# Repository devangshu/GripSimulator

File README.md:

# Grip Simulator

EE445L Final Project by Stefanie Thompson, Devangshu Goswami, Pulkit Mahajan, Anuv Gupta

## Notes

-   Password secret: `grip`
-   Serial format: `vpNum=vpValueNew\n` as `__=___...\n` ie. `03=245\n` or `12=1005\n`
    -   Two digits to represent the virtual pin number, then the full virtual pin integer value (any # of digits) followed by a newline character `\n`

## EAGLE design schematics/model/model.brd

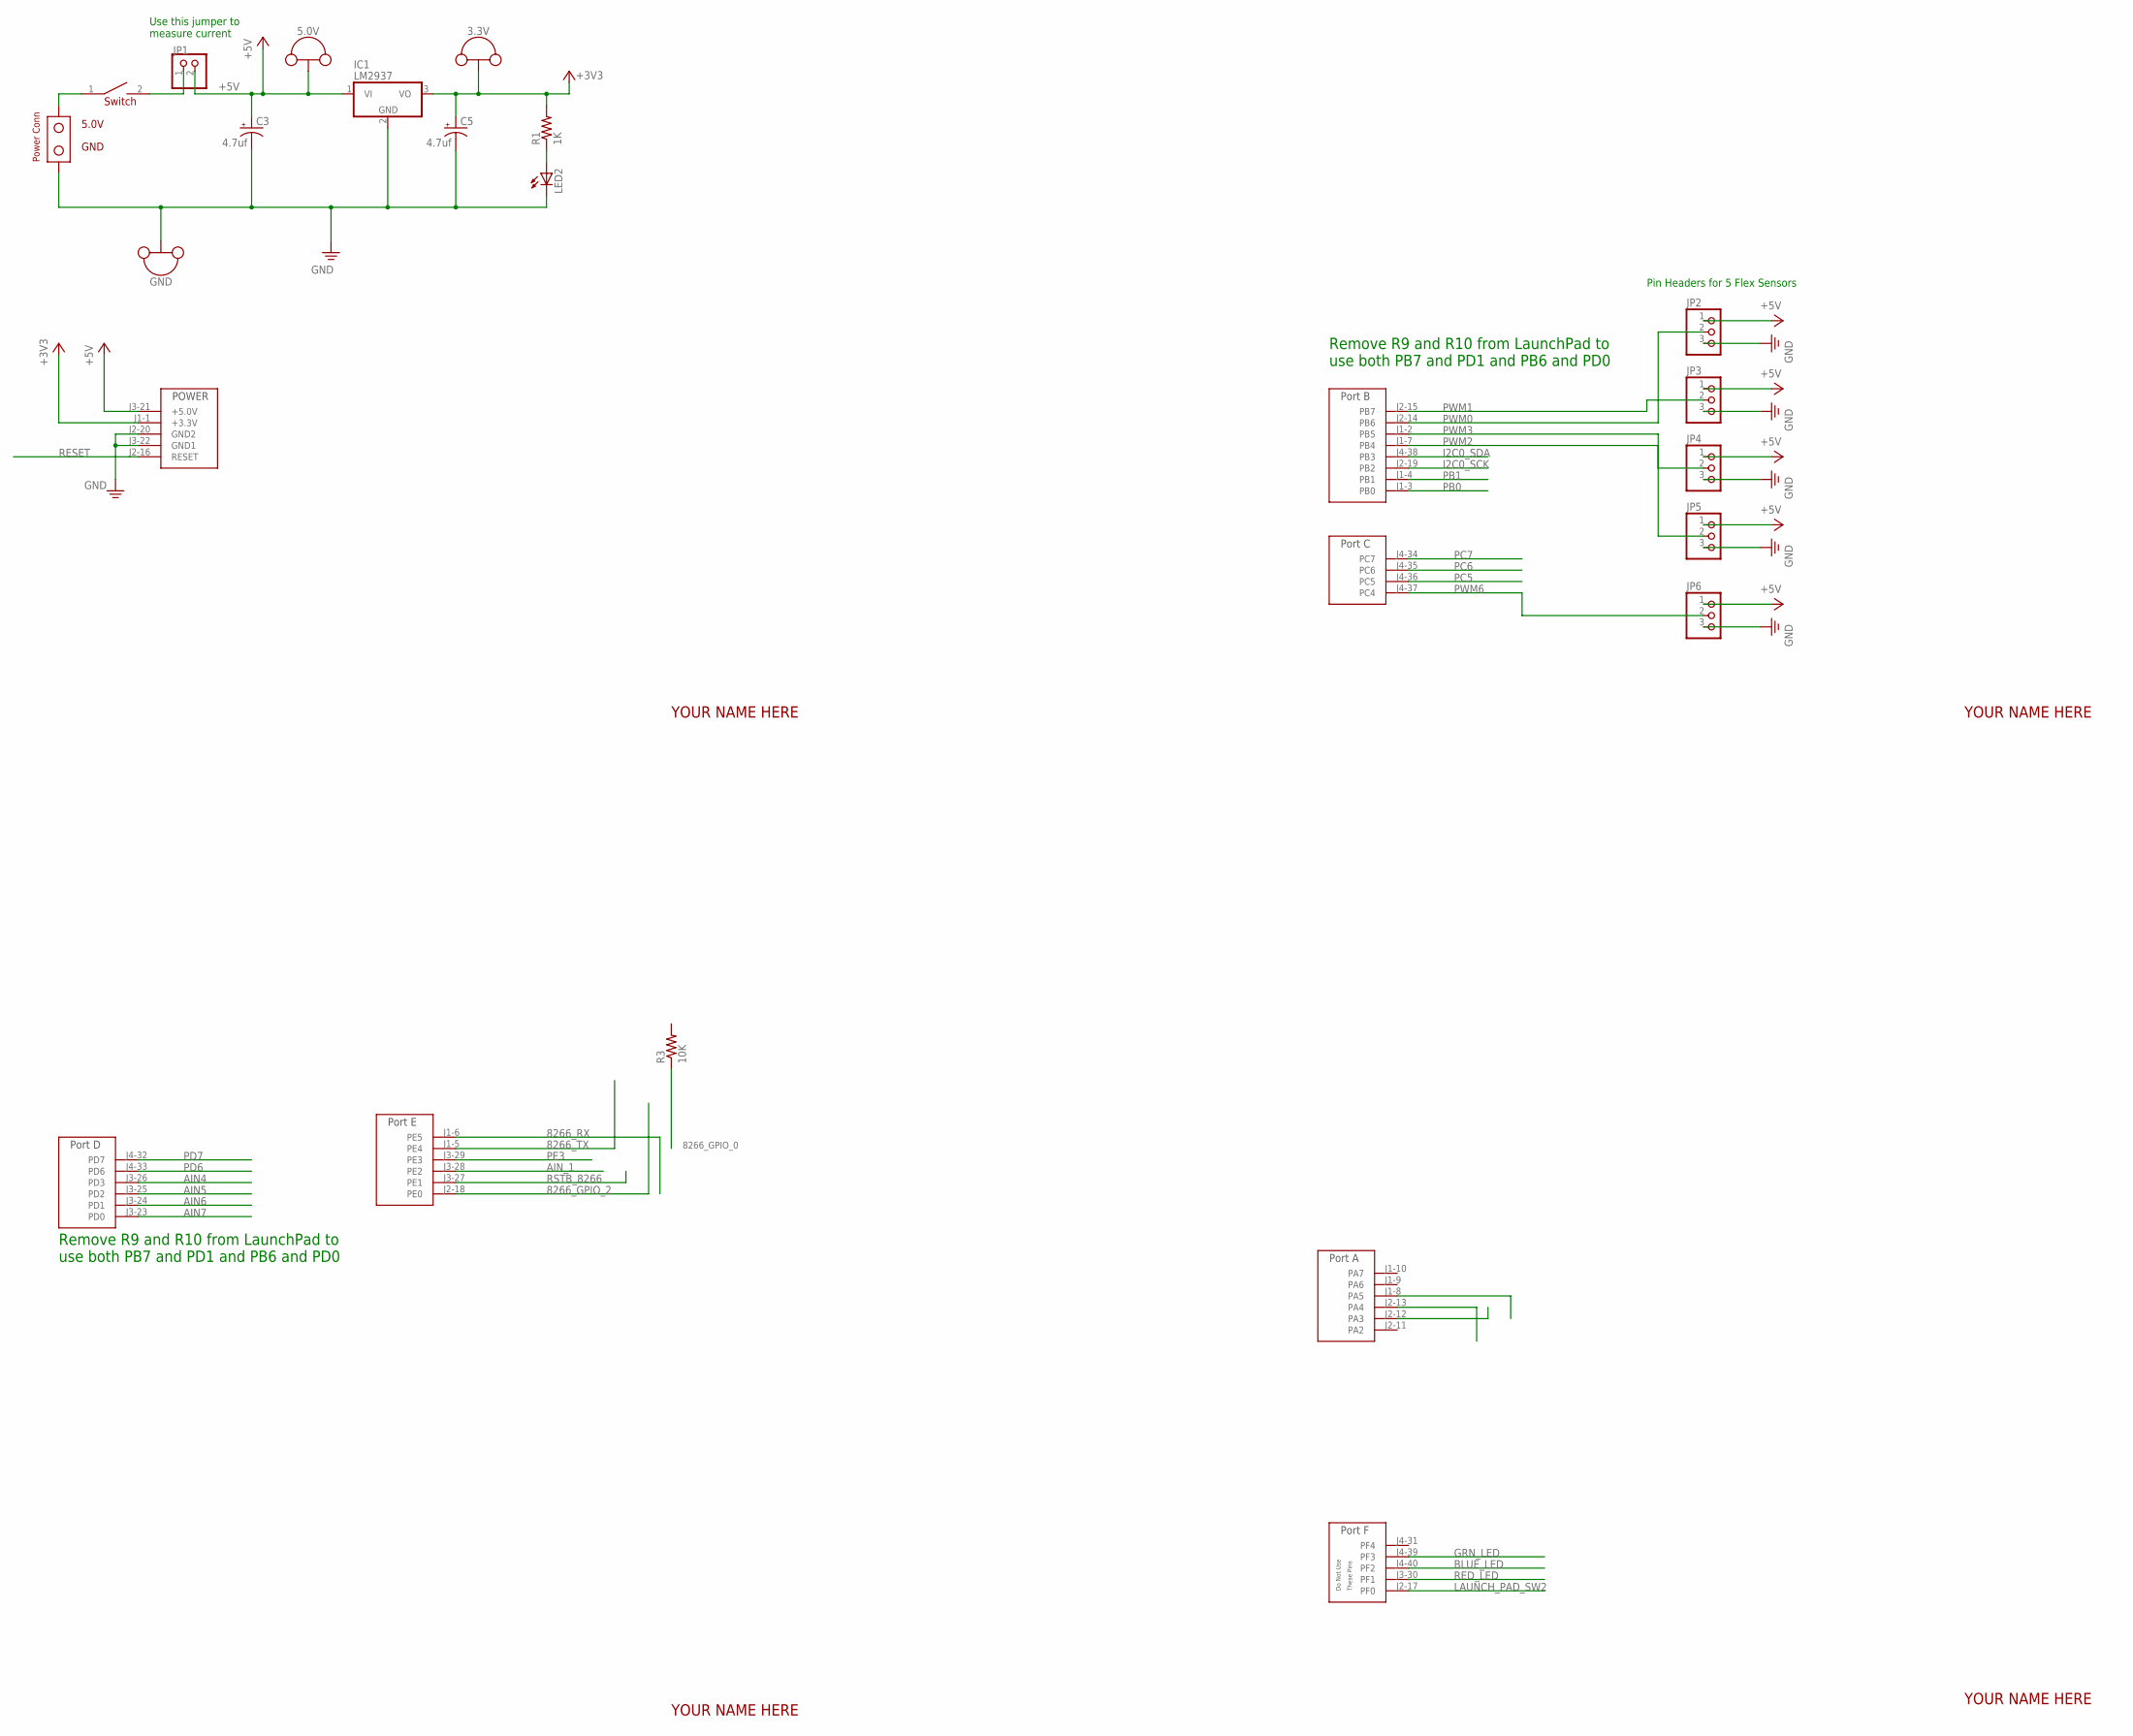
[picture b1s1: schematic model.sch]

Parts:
3.3V, 5.0V: TP_LOOP
C3, C5: 4.7uf; CAP200MILPOLARIZED
GND: TP_LOOP
IC1: LM2937; TO220
JP1: PINHD-1X2; 1X02
JP2, JP3, JP4, JP5, JP6: PINHD-1X3; 1X03
LED2: LED3MM
R1: 1K; RES200MIL
R3: 10K; RES300MIL
U$2: TM4C_BP; TM4C_BOOSTER_PACK
U$5: POWER_CONN
U$6: SW_POWER_100MIL; SW_POWER

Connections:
8266_GPIO_0: R3.1
8266_GPIO_2: U$2.J2-18 (PE0)
8266_RX: U$2.J1-6 (PE5)
8266_TX: U$2.J1-5 (PE4)
+3V3: 3.3V.P$1, 3.3V.P$2, C5.+, IC1.3 (VO), R1.2, U$2.J1-1 (+3.3V)
+5V: 5.0V.P$1, 5.0V.P$2, C3.+, IC1.1 (VI), JP1.2, JP2.1, JP3.1, JP4.1, JP5.1, JP6.1, U$2.J3-21 (+5.0V)
AIN4: U$2.J3-26 (PD3)
AIN5: U$2.J3-25 (PD2)
AIN6: U$2.J3-24 (PD1)
AIN7: U$2.J3-23 (PD0)
AIN_1: U$2.J3-28 (PE2)
BLUE_LED: U$2.J4-40 (PF2)
GND: C3.-, C5.-, GND.P$1, GND.P$2, IC1.2 (GND), JP2.3, JP3.3, JP4.3, JP5.3, JP6.3, LED2.K (C), U$2.J2-20 (GND2), U$2.J3-22 (GND1), U$5.GND
GRN_LED: U$2.J4-39 (PF3)
I2C0_SCK: U$2.J2-19 (PB2)
I2C0_SDA: U$2.J4-38 (PB3)
LAUNCH_PAD_SW2: U$2.J2-17 (PF0)
unnamed: JP1.1, U$6.2
unnamed: LED2.A, R1.1
unnamed: U$5.VDD, U$6.1
PB0: U$2.J1-3 (PB0)
PB1: U$2.J1-4 (PB1)
PC5: U$2.J4-36 (PC5)
PC6: U$2.J4-35 (PC6)
PC7: U$2.J4-34 (PC7)
PD6: U$2.J4-33 (PD6)
PD7: U$2.J4-32 (PD7)
PE3: U$2.J3-29 (PE3)
PWM0: JP2.2, U$2.J2-14 (PB6)
PWM1: JP3.2, U$2.J2-15 (PB7)
PWM2: JP4.2, U$2.J1-7 (PB4)
PWM3: JP5.2, U$2.J1-2 (PB5)
PWM6: JP6.2, U$2.J4-37 (PC4)
RED_LED: U$2.J3-30 (PF1)
RESET: U$2.J2-16 (RESET)
RSTB_8266: U$2.J3-27 (PE1)
ST7735_MISO: U$2.J2-13 (PA4)
ST7735_MOSI: U$2.J1-8 (PA5)
ST7735_TFT_CS: U$2.J2-12 (PA3)

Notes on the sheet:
Use this jumper to measure current
Remove R9 and R10 from LaunchPad to use both PB7 and PD1 and PB6 and PD0
YOUR NAME HERE
Pin Headers for 5 Flex Sensors

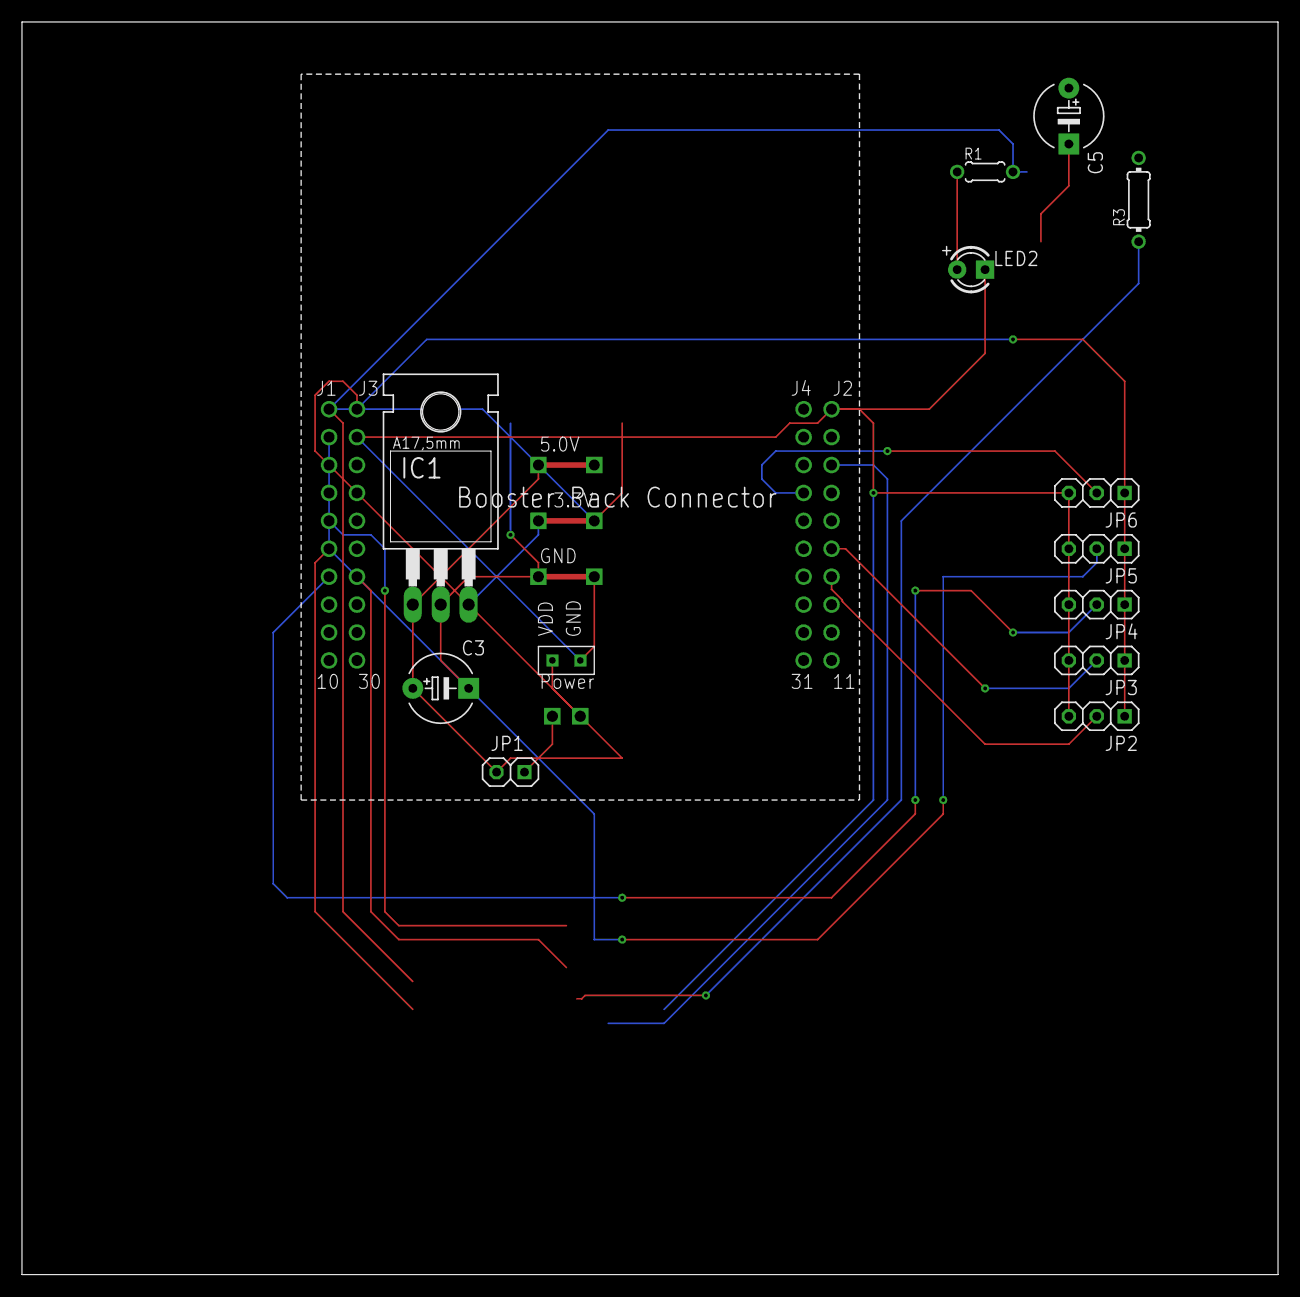
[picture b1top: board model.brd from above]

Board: 2 copper layers, 114.3 x 114.0 mm, 18 parts (0 on the bottom side), 11 nets.

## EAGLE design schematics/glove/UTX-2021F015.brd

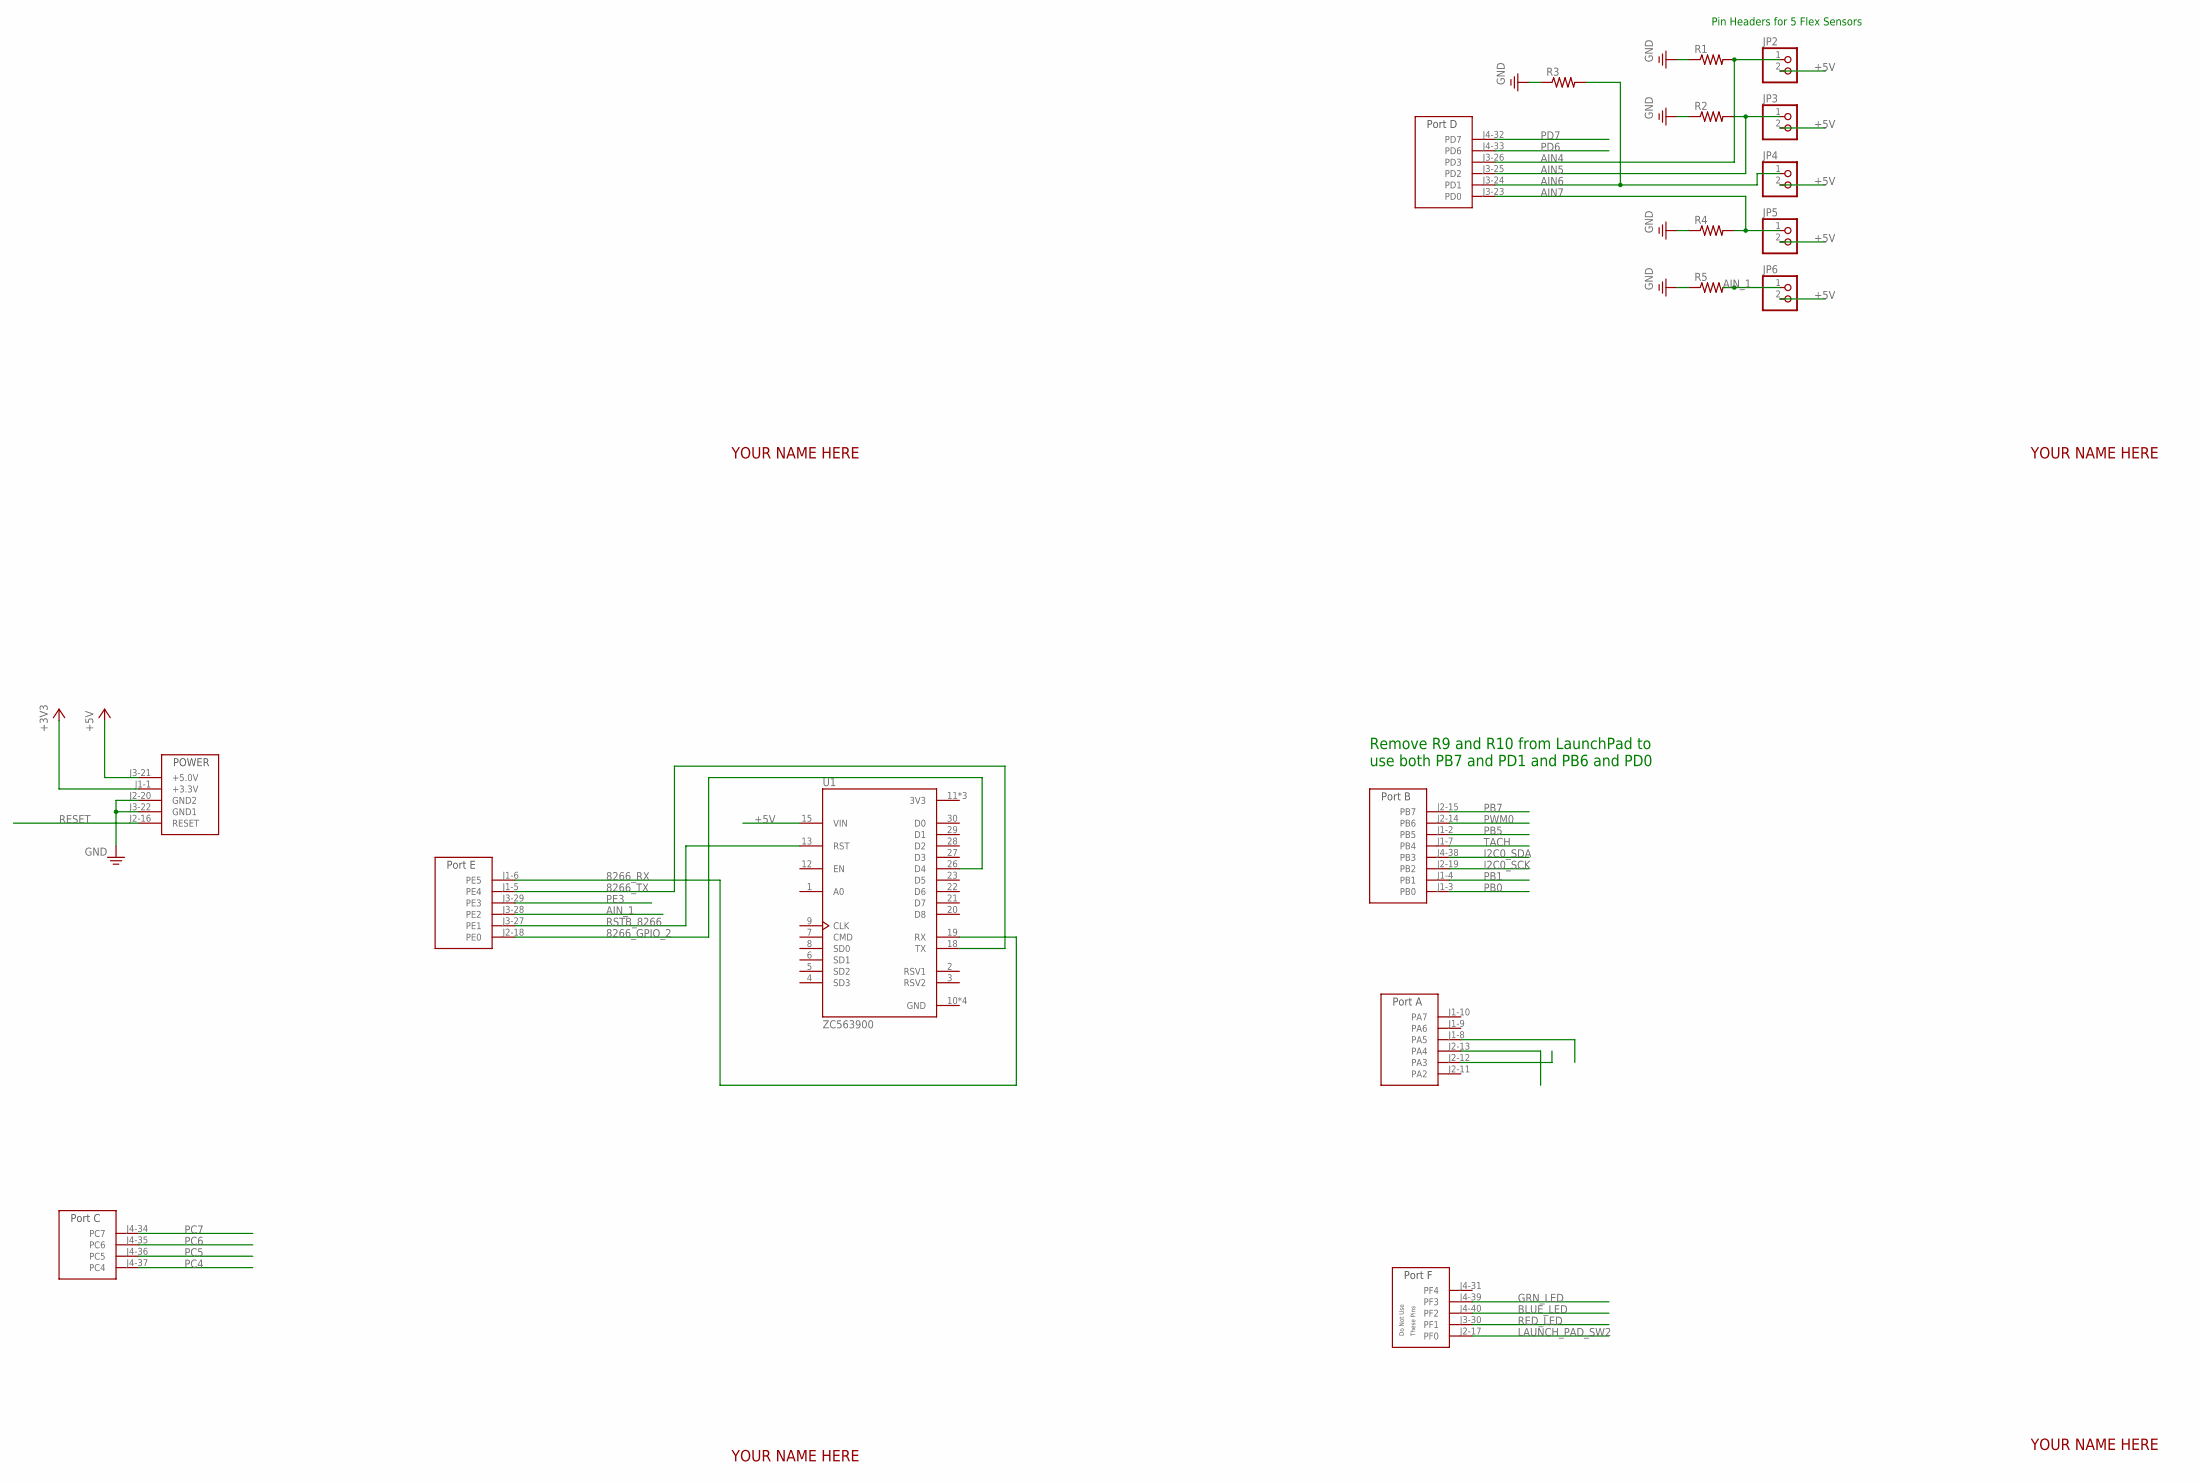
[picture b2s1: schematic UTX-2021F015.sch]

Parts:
JP2, JP3, JP4, JP5, JP6: PINHD-1X2; 1X02
R1, R2, R3, R4, R5: RESISTOR0204/7; RES300MIL
U1: ZC563900; MODULE_ZC563900
U$2: TM4C_BP; TM4C_BOOSTER_PACK

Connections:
3V3: U1.11 (3V3), U1.16 (3V3), U1.25 (3V3)
8266_GPIO_2: U1.26 (D4), U$2.J2-18 (PE0)
8266_RX: U1.19 (RX), U$2.J1-6 (PE5)
8266_TX: U1.18 (TX), U$2.J1-5 (PE4)
+3V3: U$2.J1-1 (+3.3V)
+5V: JP2.2, JP3.2, JP4.2, JP5.2, JP6.2, U1.15 (VIN), U$2.J3-21 (+5.0V)
AIN4: JP2.1, R1.2, U$2.J3-26 (PD3)
AIN5: JP3.1, R2.2, U$2.J3-25 (PD2)
AIN6: JP4.1, R3.2, U$2.J3-24 (PD1)
AIN7: JP5.1, R4.2, U$2.J3-23 (PD0)
AIN_1: JP6.1, R5.2, U$2.J3-28 (PE2)
BLUE_LED: U$2.J4-40 (PF2)
GND: R1.1, R2.1, R3.1, R4.1, R5.1, U1.10 (GND), U1.14 (GND), U1.17 (GND), U1.24 (GND), U$2.J2-20 (GND2), U$2.J3-22 (GND1)
GRN_LED: U$2.J4-39 (PF3)
I2C0_SCK: U$2.J2-19 (PB2)
I2C0_SDA: U$2.J4-38 (PB3)
LAUNCH_PAD_SW2: U$2.J2-17 (PF0)
PB0: U$2.J1-3 (PB0)
PB1: U$2.J1-4 (PB1)
PB5: U$2.J1-2 (PB5)
PB7: U$2.J2-15 (PB7)
PC4: U$2.J4-37 (PC4)
PC5: U$2.J4-36 (PC5)
PC6: U$2.J4-35 (PC6)
PC7: U$2.J4-34 (PC7)
PD6: U$2.J4-33 (PD6)
PD7: U$2.J4-32 (PD7)
PE3: U$2.J3-29 (PE3)
PWM0: U$2.J2-14 (PB6)
RED_LED: U$2.J3-30 (PF1)
RESET: U$2.J2-16 (RESET)
RSTB_8266: U1.13 (RST), U$2.J3-27 (PE1)
ST7735_MISO: U$2.J2-13 (PA4)
ST7735_MOSI: U$2.J1-8 (PA5)
ST7735_TFT_CS: U$2.J2-12 (PA3)
TACH: U$2.J1-7 (PB4)

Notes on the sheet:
Remove R9 and R10 from LaunchPad to use both PB7 and PD1 and PB6 and PD0
YOUR NAME HERE
Pin Headers for 5 Flex Sensors

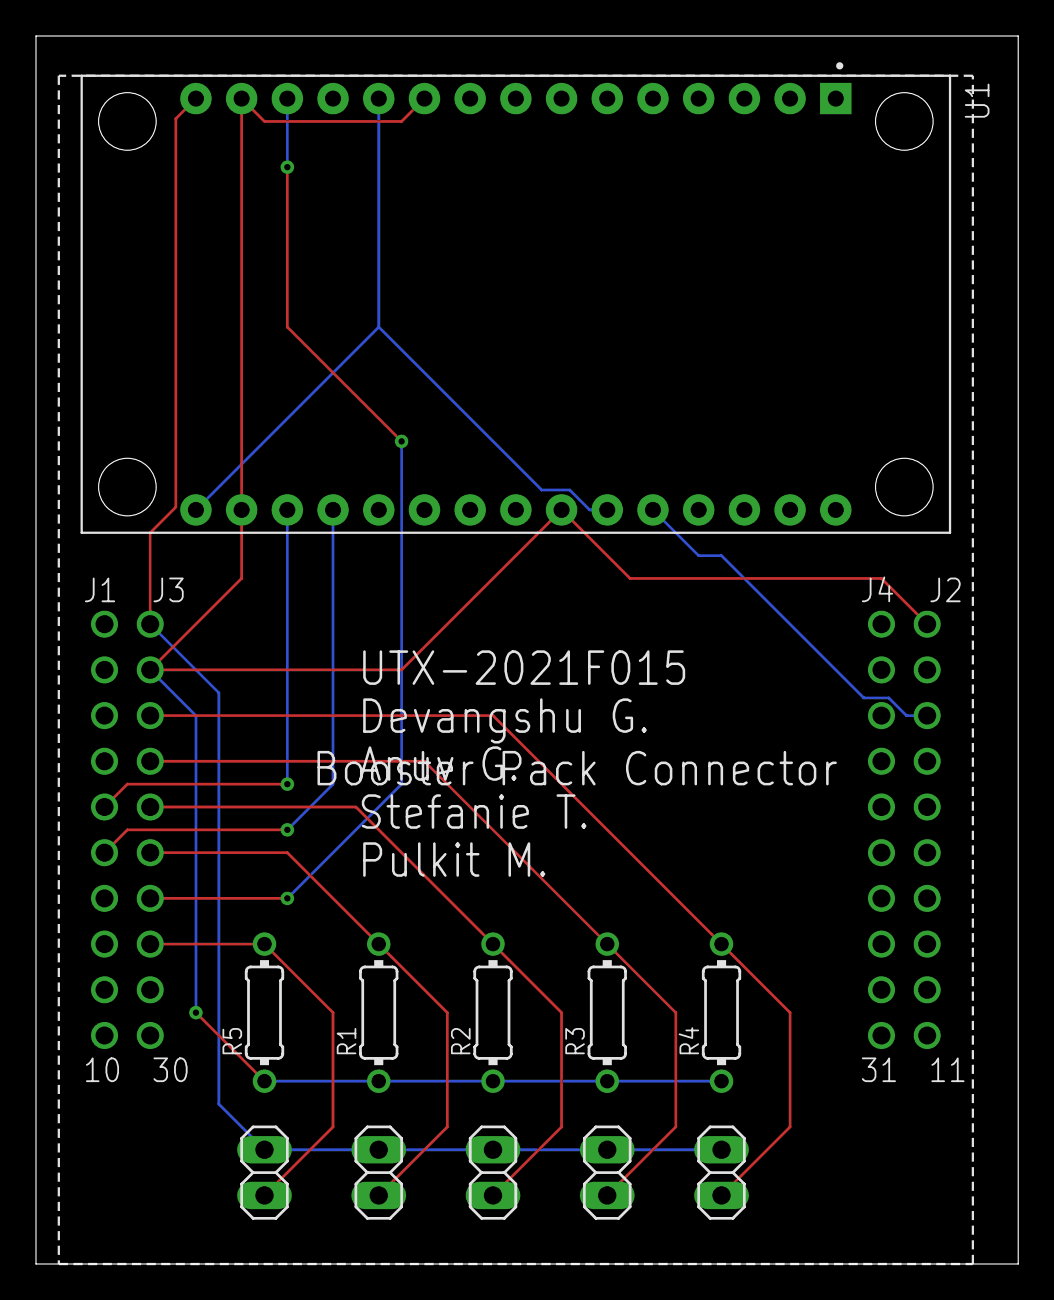
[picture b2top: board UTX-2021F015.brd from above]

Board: 2 copper layers, 54.6 x 68.2 mm, 12 parts (0 on the bottom side), 12 nets.

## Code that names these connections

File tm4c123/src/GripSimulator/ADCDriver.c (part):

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	ADC_Value = 0;
	ADC_Task = task;
	ADC_Trigger_Change = trigger_on_change;
	// ADC0_InitSWTriggerSeq3_Ch9();  // PE4
	//ADC0_InitSWTriggerSeq3_Ch7();  // PD0
	populate_LUT();
	//ADC_Init_5Chan();
	ADC0_InitSWTriggerSeq3_test(4);
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  while((SYSCTL_PRADC_R&0x0001) != 0x0001){};    // good code, but not yet implemented in simulator

  // Setting up GPIO pins for ADC input
  GPIO_PORTD_DIR_R &= ~0x0F;      // 3) make PE4-0 input
  GPIO_PORTD_AFSEL_R |= 0x0F;     // 4) enable alternate function on PE4-0
  GPIO_PORTD_DEN_R &= ~0x0F;      // 5) disable digital I/O on PE4-0
  GPIO_PORTD_PCTL_R = GPIO_PORTE_PCTL_R&0xFFFF0000;
  GPIO_PORTD_AMSEL_R |= 0x0F;     // 6) enable analog functionality on PE4-0

  ADC0_PC_R &= ~0xF;              // 8) clear max sample rate field
  ADC0_PC_R |= 0x1;               //    configure for 125K samples/sec
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  ADC0_PSSI_R = 0x000C;            // 1) initiate SS2
  while((ADC0_RIS_R&0x04)==0){};   // 2) wait for conversion done
  data[3] = ADC0_SSFIFO2_R&0xFFF;  // 3A) PE3 result
  data[2] = ADC0_SSFIFO2_R&0xFFF;  // 3A) PE2 result
  data[1] = ADC0_SSFIFO2_R&0xFFF;  // 3A) PE1 result
  data[0] = ADC0_SSFIFO2_R&0xFFF;  // 3B) PE0 result
  /*
  while((ADC0_RIS_R&0x08)==0){};   // 2) wait for conversion done
  data[4] = ADC0_SSFIFO3_R&0xFFF;  // 3) PE4 result
  */
  data[4] = 0;
  ADC0_ISC_R = 0x000C;             // 4) acknowledge completion
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      GPIO_PORTE_DEN_R &= ~0x08;  // 5.0) disable digital I/O on PE3
      GPIO_PORTE_AMSEL_R |= 0x08; // 6.0) enable analog functionality on PE3
      break;
    case 1:                       //      Ain1 is on PE2
      GPIO_PORTE_DIR_R &= ~0x04;  // 3.1) make PE2 input
      GPIO_PORTE_AFSEL_R |= 0x04; // 4.1) enable alternate function on PE2
      GPIO_PORTE_DEN_R &= ~0x04;  // 5.1) disable digital I/O on PE2
      GPIO_PORTE_AMSEL_R |= 0x04; // 6.1) enable analog functionality on PE2
      break;
    case 2:                       //      Ain2 is on PE1
      GPIO_PORTE_DIR_R &= ~0x02;  // 3.2) make PE1 input
      GPIO_PORTE_AFSEL_R |= 0x02; // 4.2) enable alternate function on PE1
      GPIO_PORTE_DEN_R &= ~0x02;  // 5.2) disable digital I/O on PE1
      GPIO_PORTE_AMSEL_R |= 0x02; // 6.2) enable analog functionality on PE1
      break;
    case 3:                       //      Ain3 is on PE0
      GPIO_PORTE_DIR_R &= ~0x01;  // 3.3) make PE0 input
      GPIO_PORTE_AFSEL_R |= 0x01; // 4.3) enable alternate function on PE0
      GPIO_PORTE_DEN_R &= ~0x01;  // 5.3) disable digital I/O on PE0
      GPIO_PORTE_AMSEL_R |= 0x01; // 6.3) enable analog functionality on PE0
      break;
    case 4:                       //      Ain4 is on PD3
      GPIO_PORTD_DIR_R &= ~0x08;  // 3.4) make PD3 input
      GPIO_PORTD_AFSEL_R |= 0x08; // 4.4) enable alternate function on PD3
      GPIO_PORTD_DEN_R &= ~0x08;  // 5.4) disable digital I/O on PD3
      GPIO_PORTD_AMSEL_R |= 0x08; // 6.4) enable analog functionality on PD3
      break;
    case 5:                       //      Ain5 is on PD2
      GPIO_PORTD_DIR_R &= ~0x04;  // 3.5) make PD2 input
      GPIO_PORTD_AFSEL_R |= 0x04; // 4.5) enable alternate function on PD2
      GPIO_PORTD_DEN_R &= ~0x04;  // 5.5) disable digital I/O on PD2
      GPIO_PORTD_AMSEL_R |= 0x04; // 6.5) enable analog functionality on PD2
      break;
    case 6:                       //      Ain6 is on PD1
      GPIO_PORTD_DIR_R &= ~0x02;  // 3.6) make PD1 input
      GPIO_PORTD_AFSEL_R |= 0x02; // 4.6) enable alternate function on PD1
      GPIO_PORTD_DEN_R &= ~0x02;  // 5.6) disable digital I/O on PD1
      GPIO_PORTD_AMSEL_R |= 0x02; // 6.6) enable analog functionality on PD1
      break;
    case 7:                       //      Ain7 is on PD0
      GPIO_PORTD_DIR_R &= ~0x01;  // 3.7) make PD0 input
      GPIO_PORTD_AFSEL_R |= 0x01; // 4.7) enable alternate function on PD0
      GPIO_PORTD_DEN_R &= ~0x01;  // 5.7) disable digital I/O on PD0
      GPIO_PORTD_AMSEL_R |= 0x01; // 6.7) enable analog functionality on PD0
      break;
    case 8:                       //      Ain8 is on PE5
      GPIO_PORTE_DIR_R &= ~0x20;  // 3.8) make PE5 input
      GPIO_PORTE_AFSEL_R |= 0x20; // 4.8) enable alternate function on PE5
      GPIO_PORTE_DEN_R &= ~0x20;  // 5.8) disable digital I/O on PE5
      GPIO_PORTE_AMSEL_R |= 0x20; // 6.8) enable analog functionality on PE5
      break;
    case 9:                       //      Ain9 is on PE4
      GPIO_PORTE_DIR_R &= ~0x10;  // 3.9) make PE4 input
      GPIO_PORTE_AFSEL_R |= 0x10; // 4.9) enable alternate function on PE4
      GPIO_PORTE_DEN_R &= ~0x10;  // 5.9) disable digital I/O on PE4
      GPIO_PORTE_AMSEL_R |= 0x10; // 6.9) enable analog functionality on PE4
      break;
    case 10:                      //       Ain10 is on PB4
      GPIO_PORTB_DIR_R &= ~0x10;  // 3.10) make PB4 input
      GPIO_PORTB_AFSEL_R |= 0x10; // 4.10) enable alternate function on PB4
      GPIO_PORTB_DEN_R &= ~0x10;  // 5.10) disable digital I/O on PB4
      GPIO_PORTB_AMSEL_R |= 0x10; // 6.10) enable analog functionality on PB4
      break;
    case 11:                      //       Ain11 is on PB5
      GPIO_PORTB_DIR_R &= ~0x20;  // 3.11) make PB5 input
      GPIO_PORTB_AFSEL_R |= 0x20; // 4.11) enable alternate function on PB5
      GPIO_PORTB_DEN_R &= ~0x20;  // 5.11) disable digital I/O on PB5
      GPIO_PORTB_AMSEL_R |= 0x20; // 6.11) enable analog functionality on PB5
      break;
  }
  SYSCTL_RCGCADC_R |= 0x00000001; // 7) activate ADC0 (actually doesn't work)
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
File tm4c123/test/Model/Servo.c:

#include <stdint.h>
#include "Servo.h"
#include "../../inc/tm4c123gh6pm.h"

void PWM0A_Init(uint16_t period, uint16_t duty){
  SYSCTL_RCGCPWM_R |= 0x01;             // 1) activate PWM0
  SYSCTL_RCGCGPIO_R |= 0x02;            // 2) activate port B
  while((SYSCTL_PRGPIO_R&0x02) == 0){};
  GPIO_PORTB_AFSEL_R |= 0x40;           // enable alt funct on PB6
  GPIO_PORTB_PCTL_R &= ~0x0F000000;     // configure PB6 as PWM0
  GPIO_PORTB_PCTL_R |= 0x04000000;
  GPIO_PORTB_AMSEL_R &= ~0x40;          // disable analog functionality on PB6
  GPIO_PORTB_DEN_R |= 0x40;             // enable digital I/O on PB6
  SYSCTL_RCC_R = 0x00100000 |           // 3) use PWM divider
      (SYSCTL_RCC_R & (~0x00010000));   //    configure for /2 divider
  PWM0_0_CTL_R = 0;                     // 4) re-loading down-counting mode
  PWM0_0_GENA_R = 0xC8;                 // low on LOAD, high on CMPA down
  // PB6 goes low on LOAD
  // PB6 goes high on CMPA down
  PWM0_0_LOAD_R = period - 1;           // 5) cycles needed to count down to 0
  PWM0_0_CMPA_R = duty - 1;             // 6) count value when output rises
  PWM0_0_CTL_R |= 0x00000001;           // 7) start PWM0
  PWM0_ENABLE_R |= 0x00000001;          // enable PB6/M0PWM0
}

void PWM0B_Init(uint16_t period, uint16_t duty){
  volatile unsigned long delay;
  SYSCTL_RCGCPWM_R |= 0x01;             // 1) activate PWM0
  SYSCTL_RCGCGPIO_R |= 0x02;            // 2) activate port B
  delay = SYSCTL_RCGCGPIO_R;            // allow time to finish activating
  GPIO_PORTB_AFSEL_R |= 0x80;           // enable alt funct on PB7
  GPIO_PORTB_PCTL_R &= ~0xF0000000;     // configure PB7 as M0PWM1
  GPIO_PORTB_PCTL_R |= 0x40000000;
  GPIO_PORTB_AMSEL_R &= ~0x80;          // disable analog functionality on PB7
  GPIO_PORTB_DEN_R |= 0x80;             // enable digital I/O on PB7
  SYSCTL_RCC_R = 0x00100000 |           // 3) use PWM divider
      (SYSCTL_RCC_R & (~0x00010000));   //    configure for /2 divider
  PWM0_0_CTL_R = 0;                     // 4) re-loading down-counting mode
  PWM0_0_GENB_R = (PWM_0_GENB_ACTCMPBD_ONE|PWM_0_GENB_ACTLOAD_ZERO);
  // PB7 goes low on LOAD
  // PB7 goes high on CMPB down
  PWM0_0_LOAD_R = period - 1;           // 5) cycles needed to count down to 0
  PWM0_0_CMPB_R = duty - 1;             // 6) count value when output rises
  PWM0_0_CTL_R |= 0x00000001;           // 7) start PWM0
  PWM0_ENABLE_R |= 0x00000002;          // enable PB7/M0PWM1
}

void PWM1A_Init(uint16_t period, uint16_t duty){
  volatile unsigned long delay;
  SYSCTL_RCGCPWM_R |= 0x01;
  SYSCTL_RCGCGPIO_R |= 0x02;
  delay = SYSCTL_RCGCGPIO_R;
  GPIO_PORTB_AFSEL_R |= 0x10; //PB4
  GPIO_PORTB_PCTL_R &= ~0x000F0000;
  GPIO_PORTB_PCTL_R |= 0x00040000;
  GPIO_PORTB_AMSEL_R &= ~0x10;
  GPIO_PORTB_DEN_R |= 0x10;
  SYSCTL_RCC_R = 0x00100000 |
      (SYSCTL_RCC_R & (~0x00010000));
  PWM0_1_CTL_R = 0;
  PWM0_1_GENA_R = 0xC8;

  PWM0_1_LOAD_R = period - 1;
  PWM0_1_CMPA_R = duty - 1;
  PWM0_1_CTL_R |= 0x00000001;
  PWM0_ENABLE_R |= 0x00000004;
}

void PWM1B_Init(uint16_t period, uint16_t duty){
  volatile unsigned long delay;
  SYSCTL_RCGCPWM_R |= 0x01;
  SYSCTL_RCGCGPIO_R |= 0x02;
  delay = SYSCTL_RCGCGPIO_R;
  GPIO_PORTB_AFSEL_R |= 0x20; //PB5
  GPIO_PORTB_PCTL_R &= ~0x00F00000;
  GPIO_PORTB_PCTL_R |= 0x00400000;
  GPIO_PORTB_AMSEL_R &= ~0x20;
  GPIO_PORTB_DEN_R |= 0x20;
  SYSCTL_RCC_R = 0x00100000 |
      (SYSCTL_RCC_R & (~0x00010000));
  PWM0_1_CTL_R = 0;
  PWM0_1_GENB_R = 0xC08;

  PWM0_1_LOAD_R = period - 1;
  PWM0_1_CMPB_R = duty - 1;
  PWM0_1_CTL_R |= 0x00000001;
  PWM0_ENABLE_R |= 0x00000008;
}

void PWM2A_Init(uint16_t period, uint16_t duty){
  volatile unsigned long delay;
  SYSCTL_RCGCPWM_R |= 0x01;
  SYSCTL_RCGCGPIO_R |= 0x10;
  delay = SYSCTL_RCGCGPIO_R;
  GPIO_PORTE_AFSEL_R |= 0x10; //PE4
  GPIO_PORTE_PCTL_R &= ~0x000F0000;
  GPIO_PORTE_PCTL_R |= 0x00040000;
  GPIO_PORTE_AMSEL_R &= ~0x10;
  GPIO_PORTE_DEN_R |= 0x10;
  SYSCTL_RCC_R = 0x00100000 |
      (SYSCTL_RCC_R & (~0x00010000));
  PWM0_2_CTL_R = 0;
  PWM0_2_GENA_R = 0xC8;

  PWM0_2_LOAD_R = period - 1;
  PWM0_2_CMPA_R = duty - 1;
  PWM0_2_CTL_R |= 0x00000001;
  PWM0_ENABLE_R |= 0x00000010;
}

void Finger0_Duty(uint16_t angle){
	uint16_t duty = toDuty(angle);
  	PWM0_0_CMPA_R = duty - 1;
}

void Finger1_Duty(uint16_t angle){
	uint16_t duty = toDuty(angle);
	PWM0_0_CMPB_R = duty - 1;
}

void Finger2_Duty(uint16_t angle){
	uint16_t duty = toDuty(angle);
	PWM0_1_CMPA_R = duty - 1;
}

void Finger3_Duty(uint16_t angle){
	uint16_t duty = toDuty(angle);
	PWM0_1_CMPB_R = duty - 1;
}

void Finger4_Duty(uint16_t angle){
	uint16_t duty = toDuty(angle);
	PWM0_2_CMPA_R = duty - 1;
}

void Hand_Init(void){
	  PWM0A_Init(PERIOD, STARTING_DUTY);
	  PWM1A_Init(PERIOD, STARTING_DUTY);
	  PWM1B_Init(PERIOD, STARTING_DUTY);
	  PWM0B_Init(PERIOD, STARTING_DUTY);
	  PWM2A_Init(PERIOD, STARTING_DUTY);
}

uint16_t toDuty (uint16_t angle){
	uint16_t duty = (11*angle) + 625;
	return duty;
}

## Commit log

2021-10-14 Final Project: Initial Commit
2021-10-14 Final Project: Started Schematic for model hand
2021-10-19 10-19 Prep: Updated Glove and Model schematics and BOMs
2021-10-24 reorganize & add backend skeleton
2021-10-24 clean up backend modules & config
2021-10-24 complete initial web/ws client
2021-10-24 refine web/ws client
2021-10-25 add navbar & logout button to web client
2021-10-25 rename api folder to backend
2021-10-25 minor backend/frontend fixes
2021-10-25 initial esp8266 glove and model drivers
2021-10-25 correct newlines
2021-10-25 clean up disconnect behavior on frontend
2021-10-25 backend tweaks & minor fixes
2021-10-25 backend production nginx proxy configuration
2021-10-25 correct spacing
2021-10-25 add backend ecosystem file
2021-10-25 remove package lock
2021-10-28 Added Valvanoware includes
2021-10-28 ADC code and updated TM4C Includes
2021-10-28 update gitignore
2021-10-28 sync commit
2021-10-29 Submitted PCB
2021-10-29 add printouts for glove pcb
2021-11-02 try to fix relative paths for ccs project includes
2021-11-02 remove extraneous files
2021-11-02 add gitkeep
2021-11-02 tweaks
2021-11-02 Revert "remove extraneous files"
    This reverts commit e9f1ebd90b6080733d336570903871a2b713bb71.
2021-11-02 sync debug files & confirm relative paths work
2021-11-02 Added basic servo drivers
2021-11-02 Modified Servo Test
2021-11-02 not working flex sensor code
2021-11-03 test adc with flex sensor, fix ccs startup code, arrange modules
2021-11-03 sync extraneous files
2021-11-03 debug glove prototype & prepare code for model (tm4c+esp)
2021-11-04 reformat, refactor, fix relative paths
2021-11-29 So this should maybe plot our adc values in real time
2021-11-30 Angle to Duty Cycle conversion complete
2021-11-30 Tested max range of senvos
2021-11-30 Created new project for model integration
2021-11-30 everything set up for tomorrow
2021-11-30 UNTESTED: Reading 5 adc channels
2021-11-30 Tested and working 5 channel ADC input
2021-11-30 Angle LUT
2021-12-01 fix esp8266 code for demo
2021-12-01 update adc driver for demo
2021-12-01 prevent spikes and sync with second laptop
2021-12-01 Changed PWM module, but 2 have same signal
2021-12-01 saving progress
2021-12-01 saving state
2021-12-01 Integrating 5 channel ADC input
2021-12-01 Test PE2
2021-12-01 modify headers for esp8266
2021-12-01 Integrated 5 channel reading for glove - untested
2021-12-01 Integrated model for 5 servos - UNTESTED
2021-12-01 adjust 3d model
2021-12-01 try this? not sure why vp2 is controlling nothing
2021-12-01 small changes for demo
2021-12-05 updated site tiny bit
2021-12-05 spacing
2022-06-24 update dependencies
2022-06-24 use env port for dash
2022-06-24 env password
2022-06-24 update password
